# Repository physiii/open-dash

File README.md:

### Objective

Provide an open source platform for vehicle information and entertainment. 

Daughterboard firmware is designed around FreeRTOS. Supports CANbus and J1850 protocols and many functions such as HVAC control, battery monitoring, vehicle status and statistics over wifi. Uses driver circuits for various actuators around the car. 

Front end software is designed to run on Linux. I recommend Ubuntu for the main computer. 

GUI is made using NodeWebkit and communicates with a custom daughterboard for interfacing with the vehicle.

### Install OS
Download ubuntu 21.10 and create boot disk  
Press esc to get to boot menu  
Boot manager  
Choose flash drive  
Choose Install ubuntu
Choose erase disk and install ubuntu  
Remove flash drive and reboot  

### Setup OS
Set no keyring passwd  
Disable Power Savings   
sudo visudo /etc/sudoers: 
```
%sudo   ALL=(ALL:ALL) NOPASSWD:ALL  
```

```
sudo usermod -a -G dialout $USER
sudo usermod -a -G audio $USER
```
Add startup programs  
```
pm2 start /usr/local/src/open-dash/service/index.js --time --name dash
nw /usr/local/src/open-dash
```

### Display

Set scale to 200%  
Rotate to portrait mode
Settings > Appearance > Position on screen: Bottom
```
sudo cp /usr/local/src/open-dash/scripts/99-touch.rules /etc/udev/rules.d/99-touch.rules
```

### Install Dependencies
```
sudo apt install -y curl
curl -sL https://deb.nodesource.com/setup_14.x | sudo -E bash -
sudo apt update
```

```
sudo wget -qnc https://repo.nordvpn.com/deb/nordvpn/debian/pool/main/nordvpn-release_1.0.0_all.deb
sudo dpkg -i ./nordvpn-release_1.0.0_all.deb
```
```
wget -q -O - https://dl-ssl.google.com/linux/linux_signing_key.pub | sudo apt-key add -
echo 'deb [arch=amd64] http://dl.google.com/linux/chrome/deb/ stable main' | sudo tee /etc/apt/sources.list.d/google-chrome.list
sudo apt update
```

```
sudo apt-get -y install gnupg
wget -qO - https://www.mongodb.org/static/pgp/server-4.4.asc | sudo apt-key add -
echo "deb [ arch=amd64,arm64 ] https://repo.mongodb.org/apt/ubuntu focal/mongodb-org/4.4 multiverse" | sudo tee /etc/apt/sources.list.d/mongodb-org-4.4.list
```

```
sudo apt update && sudo apt upgrade -y

sudo apt install -y \
  tmux git nodejs sshfs nmap cmake pv vlc pithos gimp librecad resolvconf openssh-server \
  net-tools v4l-utils clementine net-tools kodi nordvpn vlc-plugin-bittorrent \
  libgconf-2-4 sshpass git nodejs dnsmasq hostapd tmux xdotool libudev-dev \
  python-setuptools python3-dev libssl-dev libasound2-dev nmap ffmpeg \
  build-essential cmake pkg-config libjpeg-dev libtiff5-dev libatomic1 \
  libavcodec-dev libavformat-dev libswscale-dev libv4l-dev libxvidcore-dev libx264-dev libfreetype6-dev \
  libatlas-base-dev gfortran python3-dev libavcodec-dev libavformat-dev python3-pip \
  libasound-dev portaudio19-dev libportaudio2 libportaudiocpp0 \
  google-chrome-stable speedtest-cli mongodb-org \

```

```
sudo npm install -g nw-gyp
sudo npm install -g pm2 --unsafe-perm=true --allow-root
sudo snap install atom --classic
sudo snap install blender --channel=beta --classic
```

```
sudo apt install -y apt-transport-https curl
sudo curl -fsSLo /usr/share/keyrings/brave-browser-archive-keyring.gpg https://brave-browser-apt-release.s3.brave.com/brave-browser-archive-keyring.gpg
echo "deb [signed-by=/usr/share/keyrings/brave-browser-archive-keyring.gpg arch=amd64] https://brave-browser-apt-release.s3.brave.com/ stable main"|sudo tee /etc/apt/sources.list.d/brave-browser-release.list
sudo apt update
sudo apt install -y brave-browser
```
### kicad
```
sudo add-apt-repository --yes ppa:js-reynaud/kicad-5.1
sudo apt update
sudo apt install -y --install-suggests kicad

mkdir ~/circuits
cd ~/circuits
git clone https://github.com/physiii/kicad-parts
# add symbol and footprint paths
```
### esp32
```
sudo ln -s /usr/bin/python3 /usr/bin/python

mkdir -p ~/esp
cd ~/esp
git clone --recursive https://github.com/espressif/esp-idf.git

cd ~/esp/esp-idf
./install.sh

echo "alias get_idf='. $HOME/esp/esp-idf/export.sh'" >> ~/.bashrc

source ~/.bashrc
get_idf

cd ~/esp
cp -r $IDF_PATH/examples/get-started/hello_world .
cd ~/esp/hello_world
idf.py set-target esp32
idf.py menuconfig
```

### audio
```
cd ~
git clone https://github.com/physiii/ardour-sessions

```
sudo nano /etc/security/limits.conf
```
  @audio          -       rtprio          99
```
```
sudo apt install -y qjackctl pulseaudio-module-jack libjack0 jackd jack-tools \
linux-lowlatency ardour a2jmidid libjack-dev pavucontrol \
```
## Jack
set interface  
Settings -> MIDI Driver: seq  
Options -> execute script after startup: pactl load-module module-jack-sink;pactl load-module module-jack-source;pactl set-default-sink jack_out  
Misc -> start JACK audio service on application startup  
```
pamcd set-default-sink jack_out
```
```
sudo apt install -y \
calf-plugins libtool autoconf libexpat1-dev libglib2.0-dev libfluidsynth-dev \
jackd libjack-dev libglade2-dev lv2-dev yoshimi ams \
blop caps cmt fil-plugins rev-plugins swh-plugins tap-plugins \
invada-studio-plugins-lv2 mda-lv2 swh-lv2 \
blepvco mcp-plugins omins so-synth-lv2 lingot \
```
## MIDI

```
pip3 install python-rtmidi pyserial mido
git clone https://github.com/physiii/wireless-midi
```

###  Popcorn
```
sudo chown -R ${USER}:${USER} /usr/local/src
cd /usr/local/src
git clone https://github.com/popcorn-official/popcorn-desktop
cd popcorn-desktop
sudo npm install -g gulp
npm install
gulp build
gulp run
nw .
```
### NW.JS
```
sudo chown -R ${USER}:${USER} /usr/local/src
cd /usr/local/src  
wget https://dl.nwjs.io/v0.54.0/nwjs-sdk-v0.54.0-linux-x64.tar.gz
tar -zxvf nwjs-sdk*  
cd nwjs-sdk*  
sudo ln -s /usr/local/src/nwjs-sdk-v0.54.0-linux-x64/nw /usr/bin/nw  
```
### Install Software
```
sudo chown -R ${USER}:${USER} /usr/local/src
cd /usr/local/src
git clone https://github.com/physiii/open-dash
cd open-dash
npm install
npm run build
```

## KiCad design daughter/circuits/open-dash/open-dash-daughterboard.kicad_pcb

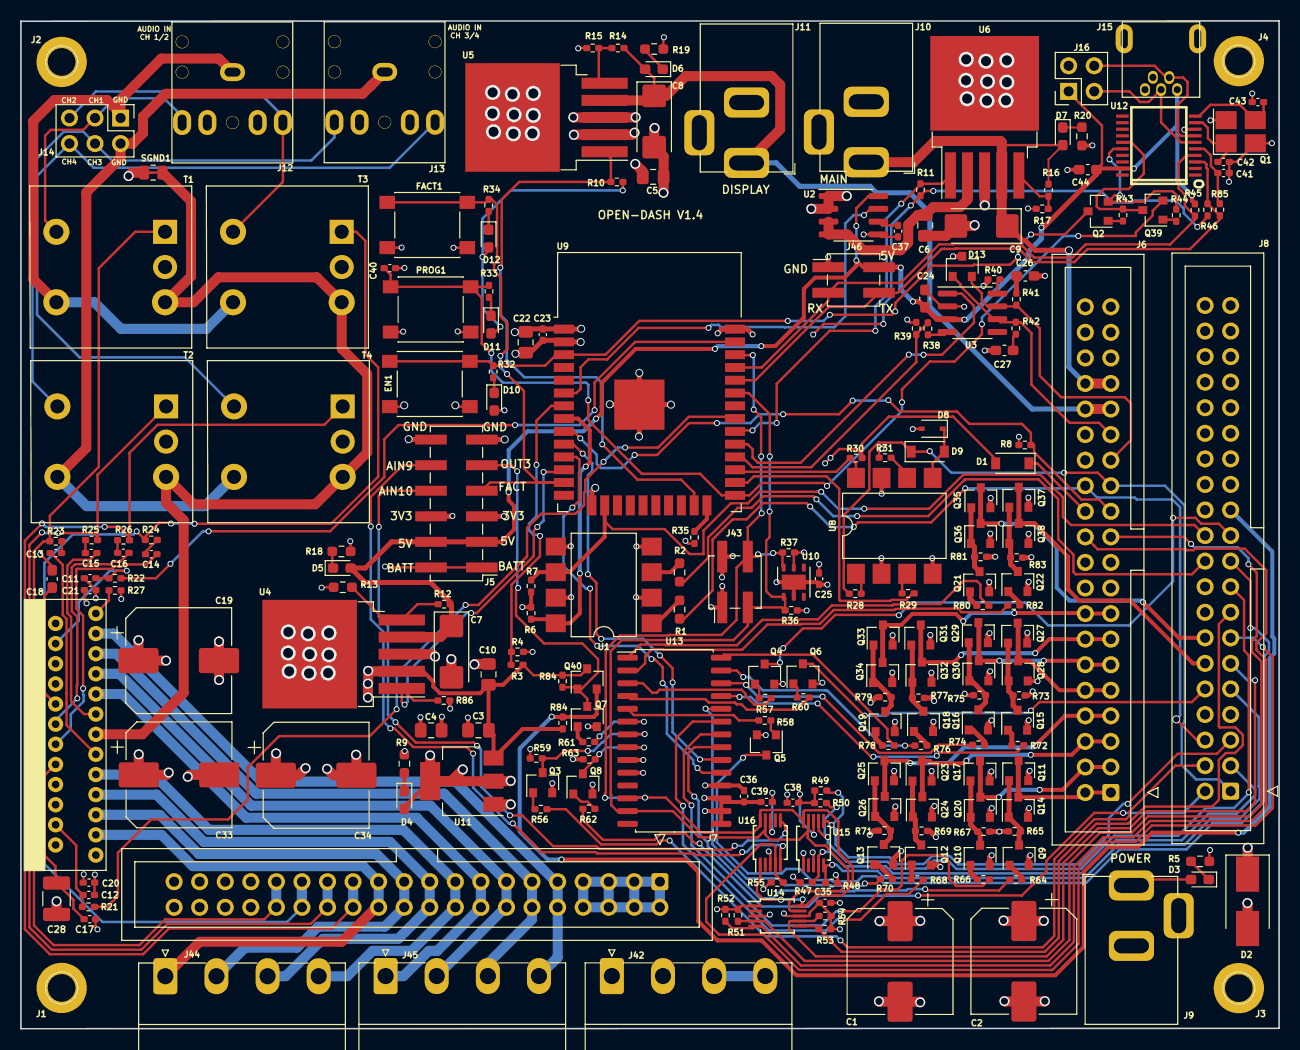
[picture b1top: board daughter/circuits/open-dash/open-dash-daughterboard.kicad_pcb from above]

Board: 4 copper layers, 125.0 x 100.1 mm, 225 parts (0 on the bottom side), 170 nets.

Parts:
C1, C2, C19, C33, C34: C_470uF; CP_Elec_10x10
C3, C4, C5, C6, C10, C22: C_10uF; C_0805_2012Metric_Pad1.18x1.45mm_HandSolder
C7, C8, C9: C_10uF_Ta; CP_EIA-6032-15_Kemet-U_Pad2.25x2.35mm_HandSolder
C11, C12, C17, C20, C23, C40: C_1uF; C_0402_1005Metric_Pad0.74x0.62mm_HandSolder
C13, C14, C15, C16, C21, C25: C_0.1uF; C_0402_1005Metric_Pad0.74x0.62mm_HandSolder
C18: C_470nF; C_0603_1608Metric_Pad1.08x0.95mm_HandSolder
C24: C_0.1uF; C_0603_1608Metric_Pad1.08x0.95mm_HandSolder
C26, C27: C_470pF; C_0603_1608Metric_Pad1.08x0.95mm_HandSolder
C28: C_47uF; C_1210_3225Metric_Pad1.33x2.70mm_HandSolder
C35, C36, C38, C39, C41: C_100nF_0402; C_0402_1005Metric_Pad0.74x0.62mm_HandSolder
C37: C_1nF_0402; C_0402_1005Metric_Pad0.74x0.62mm_HandSolder
C42, C43: C_27pF_0402; C_0402_1005Metric_Pad0.74x0.62mm_HandSolder
C44: C_22uF; C_0603_1608Metric_Pad1.08x0.95mm_HandSolder
D1, D9: D_B5819W; D_SOD-123
D2: D_Zener; D_SMB_Handsoldering
D3, D4, D5, D6, D7: LED_G; LED_0603_1608Metric_Pad1.05x0.95mm_HandSolder
D8: MM3Z8V2; D_SOD-323
D10, D11, D12: LED_G; D_0603_1608Metric_Pad1.05x0.95mm_HandSolder
D13: PESD1CAN-UX; SOT-23
EN1: SW_PUSH; SW_SPST_PTS645
FACT1: SW_PUSH; SW_SPST_PTS645
J1, J2, J3, J4: Conn_01x01_Female; Mount_Hole
J5: Conn_02x06_Odd_Even; PinHeader_2x06_P2.54mm_Vertical_SMD
J6, J7, J8: Conn_IDE_40; IDC-Header_2x20_P2.54mm_Vertical
J9, J10, J11: Barrel_Jack_OD5.5_ID2.5; BarrelJack_OD5.5_ID2.5
J12, J13: AudioJack_3.5TRS; AudioJack_SJ1-3525N
J14: Conn_02x03_Odd_Even; PinHeader_2x03_P2.54mm_Vertical
J15: USB_MINI_B; USB-mini-B-0548190519
J16: Conn_02x02_Counter_Clockwise; PinHeader_2x02_P2.54mm_Vertical
J42, J44, J45: Terminal_01x04; Terminal_1,5_4-G-5.08_1x04_P5.08mm_Horizontal
J43, J46: Conn_02x02_Counter_Clockwise; PinHeader_2x02_P2.54mm_Vertical_SMD
PROG1: SW_PUSH; SW_SPST_PTS645
Q1: Crystal_12Mhz; Crystal_SMD_3225-4Pin_3.2x2.5mm_HandSoldering
Q2: Q_SS8050; SOT-23
Q3, Q4, Q5, Q6, Q7, Q8, Q9, Q10, Q12, Q13, Q15, Q16, Q18, Q19, Q21, Q22: Q_NPN_BEC; SOT-23
Q11, Q17, Q23, Q25, Q27, Q29, Q31, Q33, Q35, Q37, Q40: Q_AO3401A; SOT-23
Q14, Q20, Q24, Q26, Q28, Q30, Q32, Q34, Q36, Q38: Q_AO3400A; SOT-23
Q39: Q_SS8550; SOT-23
R1, R2, R5, R9, R18, R19, R20: R_1K; R_0603_1608Metric_Pad0.98x0.95mm_HandSolder
R3: R_100K_0402; R_0402_1005Metric_Pad0.72x0.64mm_HandSolder
R4, R6, R7, R10, R11, R21, R32, R33, R34, R35, R36, R37, R39, R45, R46, R47, R48, R49, R50, R51, R52, R53, R54, R55, R56, R57, R58, R59, R60, R61, R62, R63, R64, R65, R66, R67, R68, R69, R70, R71, R72, R73, R74, R75, R76, R77, R78, R79, R80, R81, R82, R83, R84#2, R85, R86: R_10K_0402; R_0402_1005Metric_Pad0.72x0.64mm_HandSolder
R8, R23, R24, R25, R26, R28, R30, R31, R43, R44, R84: R_1K_0402; R_0402_1005Metric_Pad0.72x0.64mm_HandSolder
R12, R14, R16: R_20K; R_0402_1005Metric_Pad0.72x0.64mm_HandSolder
R13: R_6.8K; R_0603_1608Metric_Pad0.98x0.95mm_HandSolder
R15, R17: R_2.2K; R_0402_1005Metric_Pad0.72x0.64mm_HandSolder
R22, R27: R_47K_0402; R_0402_1005Metric_Pad0.72x0.64mm_HandSolder
R29, R41, R42: R_100; R_0402_1005Metric_Pad0.72x0.64mm_HandSolder
R38, R40: R_4.7K; R_0402_1005Metric_Pad0.72x0.64mm_HandSolder
SGND1: SGND_CONN
T1, T2, T3, T4: Audio_Transformer
U1, U8: Opto_TLP521; SMDIP-8_W9.53mm
U2: ACS711; SOIC-8_3.9x4.9mm_P1.27mm
U3: CAN_MCP2551-I-SN; SOIC-8_3.9x4.9mm_P1.27mm
U4, U5, U6: MIC29302WU; TO-263-5_TabPin3
U7: TDA7851F; Flexiwatt25-V
U9: ESP32-WROOM-32
U10: Temp_Hum_HDC1080DMBR; DFN-6-1EP_3x3mm_P1mm_EP1.5x2.4mm
U11: REG_AMS1117-3.3; SOT-223-3_TabPin2
U12: CH340T(SSOP20W); SSOP-20W
U13: MCP23017_SS; SOIC-28W_7.5x17.9mm_P1.27mm
U14, U15, U16: ADC_ADS1015; MSOP-10_3x3mm_P0.5mm

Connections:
/3V3: C4.1, C22.1, C23.1, C25.1, C35.1, C36.1, C38.1, C39.1, D1.2, D4.2, D10.2, D11.2, D12.2, J5.5, J5.6, J43.2, R6.2, R7.2, R10.2, R11.2, R30.1, R36.1, R37.2, R46.2, R47.2, R48.2, R49.2, R50.2, R51.2, R52.2, R53.2, R54.2, R55.2, R59.2, R63.2, R86.2, U9.2, U10.5, U11.2, U13.9, U13.18, U14.1, U14.8, U15.8, U16.8
/5V: C7.1, C24.1, C44.1, D5.2, J5.3, J5.4, J15.1, J16.1, J46.2, R12.1, R45.1, U2.8, U3.3, U4.4, U12.19
/5V_EN: R86.1, U4.1, U9.12
/AIN9: J5.10, U16.5
/AIN10: J5.8, U16.6
/AMBIENT_AIR_TEMP: J8.9, R48.1, U15.5
/AMBIENT_LIGHT: J8.15, R53.1, U14.6
/AUDIO_IN1: J7.31, J7.32, R23.2, T1.5
/AUDIO_IN2: J7.29, J7.30, R24.2, T3.5
/AUDIO_IN3: J7.27, J7.28, R25.2, T2.5
/AUDIO_IN4: J7.25, J7.26, R26.2, T4.5
/AUDIO_MUTE: R22.2, U9.37
/AUDIO_STBY: R21.1, U9.31
/Audio Amplifier/AC_GND: C18.1, U7.16
/Audio Amplifier/AUDIO_GND1: J12.1, J14.1, T1.2, T3.2
/Audio Amplifier/AUDIO_GND2: J13.1, J14.2, T2.2, T4.2
/Audio Amplifier/IN1: J12.3, J14.3, T1.1
/Audio Amplifier/IN2: J12.2, J14.5, T3.1
/Audio Amplifier/IN3: J13.3, J14.4, T2.1
/Audio Amplifier/IN4: J13.2, J14.6, T4.1
/Audio Amplifier/MUTE: C11.2, R22.1, U7.22
/Audio Amplifier/OD: R27.2, U7.25
/Audio Amplifier/STBY: C12.2, R21.2, U7.4
/Audio Amplifier/SVR: C17.1, C28.1, U7.10
/BATTERY: C1.1, C2.1, C3.1, C5.1, C10.1, C19.1, C20.2, C21.1, C33.1, C34.1, D2.1, D3.2, J5.1, J5.2, J6.17, J6.18, J6.19, J6.20, J6.28, J7.1, J7.2, J7.3, J7.4, J7.5, J7.6, J7.7, J7.8, J8.8, J8.18, J8.27, J8.28, J8.29, J8.30, J8.31, J8.32, J9.1, J42.3, J42.4, Q11.2, Q17.2, Q23.2, Q25.2, Q27.2, Q29.2, Q31.2, Q33.2, Q35.2, Q37.2, Q40.3, R3.1, R31.1, R65.2, R67.2, R69.2, R71.2, R73.2, R75.2, R77.2, R79.2, R81.2, R83.2, R84.1, R84#2.2, U2.1, U2.2, U4.2, U5.2, U7.6, U7.20, U11.3
/BATTERY_VOLTAGE_SENSE: R3.2, R4.1, U9.7
/BLOWER_MOTOR: J8.10, Q6.3
/CAN+: D13.2, J6.27, R41.2, U3.7
/CAN-: D13.1, J6.29, R42.2, U3.6
/CAN_RX: R38.1, R39.2, U9.28
/CAN_TX: U3.1, U9.29
/CANbus/RX: R38.2, U3.4
/CURRENT_SENSE: U2.7, U9.6
/C_OUT3: J5.9, Q7.3, Q40.1, R84#2.1
/DISPLAY_EN: R10.1, U5.1, U9.23
/DISPLAY_POWER: C8.1, D6.2, J6.31, J6.32, J11.1, R14.1, U5.4
/DRIVER_HEATED_SEAT_STATUS: J8.4, R56.1
/DRIVER_SEAT_TEMP_CONTROL: J8.14, Q35.3, Q36.3
/DRIVER_SUNLOAD: J8.11, R54.1, U14.7
/ESP_EN: EN1.1, Q2.3, R32.1, U9.3
/EXT_AMP_ON: J8.23, Q40.2, R84.2
/FACT: FACT1.1, J5.7, R34.1, U9.13
/HVAC/A0: R64.1, U13.21
/HVAC/A1: R66.1, U13.22
/HVAC/A2: R68.1, U13.23
/HVAC/A3: R70.1, U13.24
/HVAC/A4: R72.1, U13.25
/HVAC/A5: R74.1, U13.26
/HVAC/A6: R76.1, U13.27
/HVAC/A7: R78.1, U13.28
/HVAC/B0: R80.1, U13.1
/HVAC/B1: R82.1, U13.2
/HVAC/B2: R57.1, U13.3
/HVAC/B3: R60.1, U13.4
/HVAC/B4: R58.1, U13.5
/HVAC/B5: R61.1, U13.6
/HVAC/B6: Q3.3, R59.1, U13.7
/HVAC/B7: Q8.3, R63.1, U13.8
/HVAC/H-Bridge/C1: Q9.3, Q11.1, Q14.1, R65.1
/HVAC/H-Bridge/C2: Q10.3, Q17.1, Q20.1, R67.1
/HVAC/sheet607B7BA9/C1: Q21.3, Q35.1, Q36.1, R81.1
/HVAC/sheet607B7BA9/C2: Q22.3, Q37.1, Q38.1, R83.1
/HVAC/sheet60537A7E/C1: Q15.3, Q27.1, Q28.1, R73.1
/HVAC/sheet60537A7E/C2: Q16.3, Q29.1, Q30.1, R75.1
/HVAC/sheet60537FF7/C1: Q18.3, Q31.1, Q32.1, R77.1
/HVAC/sheet60537FF7/C2: Q19.3, Q33.1, Q34.1, R79.1
/HVAC/sheet6051923C/C1: Q12.3, Q23.1, Q24.1, R69.1
/HVAC/sheet6051923C/C2: Q13.3, Q25.1, Q26.1, R71.1
/IGNITION: J6.26, J8.6, R1.2
/IGNITION_SENSE: R6.1, U1.8, U9.8
/INSIDE_AIR_TEMP: J8.3, R47.1, U15.4
/INSIDE_AIR_TEMP_BLOWER: J8.21, Q4.3
/INTA: U9.10, U13.20
/INTB: U9.11, U13.19
/J1850: D9.1, J6.25, J8.1, R28.2
/J1850_RX: R30.2, U8.8, U9.27
/J1850_TX: R29.1, U9.26
/LEFT_AIR_TEMP_CONTROL_A: J6.1, J6.2, Q11.3, Q14.3
/LEFT_AIR_TEMP_CONTROL_B: J6.3, J6.4, Q17.3, Q20.3
/LF+: J7.17, J7.18, J44.4, U7.9
/LF-: J7.19, J7.20, J44.3, U7.7
/LOWER_LEFT_AIR_TEMP: J6.22, R52.1, U14.5
/LOWER_RIGHT_AIR_TEMP: J6.21, R51.1, U14.4
/LR+: J7.15, J7.16, J45.1, U7.17
/LR-: J7.13, J7.14, J45.2, U7.19
/MAIN_EN: R11.1, U6.1, U9.30
/MAIN_POWER: C9.1, D7.2, J6.33, J6.34, J10.1, R16.1, U6.4
/MODE_A: J6.9, J6.10, Q27.3, Q28.3
/MODE_B: J6.11, J6.12, Q29.3, Q30.3
/Microcontroller/IO2: R35.1, U9.24
/PASSENGER_HEATED_SEAT_STATUS: J8.2, R62.1
/PASSENGER_SEAT_TEMP_CONTROL: J8.12, Q37.3, Q38.3
/PASSENGER_SUNLOAD: J8.13, R55.1, U16.4
/PROG: C40.1, PROG1.1, Q39.2, R33.1, U9.25
/Power/MAIN_POWER_IN: C6.1, U2.3, U2.4, U6.2
/REAR_DEFOG: J8.19, Q5.3
/RECIRCULATION_A: J6.13, J6.14, Q31.3, Q32.3
/RECIRCULATION_B: J6.15, J6.16, Q33.3, Q34.3
/RF+: J7.21, J7.22, J44.2, U7.5
/RF-: J7.23, J7.24, J44.1, U7.3
/RIGHT_AIR_TEMP_CONTROL_A: J6.5, J6.6, Q23.3, Q24.3
/RIGHT_AIR_TEMP_CONTROL_B: J6.7, J6.8, Q25.3, Q26.3
/RR+: J7.11, J7.12, J45.3, U7.21
/RR-: J7.9, J7.10, J45.4, U7.23
/RXD: J46.4, R46.1, R85.2, U9.34, U12.3
/SCL: J43.4, R37.1, U9.36, U10.6, U13.12, U14.10, U15.10, U16.1, U16.10
/SDA: J43.3, R36.2, U9.33, U10.1, U13.13, U14.9, U15.9, U16.9
/SENSE1: J8.22, R7.1, U1.6, U9.16
/TRIGGER1: J8.20, R2.2
/TXD: J46.3, R45.2, U9.35, U12.4
/UPPER_LEFT_AIR_TEMP: J8.17, R50.1, U15.7
/UPPER_RIGHT_AIR_TEMP: J8.5, R49.1, U15.6
/USB/D+: J15.3, J16.3, U12.6
/USB/D-: J15.2, J16.4, U12.7
/WHEEL_CONTROLS_SIGNAL: J6.23, R8.2, U9.9
/WHEEL_CONTROLS_SUPPLY: D1.1, J6.24
GND: C1.2, C2.2, C3.2, C4.2, C5.2, C6.2, C7.2, C8.2, C9.2, C10.2, C11.1, C12.1, C17.2, C18.2, C19.2, C20.1, C21.2, C22.2, C23.2, C24.2, C25.2, C26.2, C27.2, C28.2, C33.2, C34.2, C35.2, C36.2, C37.2, C38.2, C39.2, C40.2, C41.2, C42.2, C43.2, C44.2, D2.2, D8.2, D13.3, EN1.2, FACT1.2, J1.1, J2.1, J3.1, J4.1, J5.11, J5.12, J6.30, J6.35, J6.36, J6.37, J6.38, J6.39, J6.40, J7.33, J7.34, J7.35, J7.36, J7.37, J7.38, J7.39, J7.40, J8.7, J8.24, J8.25, J8.26, J8.33, J8.34, J8.35, J8.36, J8.37, J8.38, J8.39, J8.40, J9.2, J9.3, J10.2, J10.3, J11.2, J11.3, J15.5, J16.2, J42.1, J42.2, J43.1, J46.1, PROG1.2, Q1.2, Q1.4, Q3.2, Q4.2, Q5.2, Q6.2, Q7.2, Q8.2, Q9.2, Q10.2, Q12.2, Q13.2, Q14.2, Q15.2, Q16.2, Q18.2, Q19.2, Q20.2, Q21.2, Q22.2, Q24.2, Q26.2, Q28.2, Q30.2, Q32.2, Q34.2, Q36.2, Q38.2, R4.2, R5.1, R8.1, R9.2, R13.2, R15.2, R17.2, R18.2, R19.2, R20.2, R27.1, R35.2, R39.1, R40.1, SGND1.1, U1.2, U1.4, U1.5, U1.7, U2.5, U3.2, U4.3, U5.3, U6.3, U7.1, U7.2, U7.8, U7.18, U7.24, U8.2, U8.4, U8.7, U9.1, U9.15, U9.38, U9.39, U10.2, U10.7, U11.1, U12.8, U13.10, U13.15, U13.16, U13.17, U14.3, U15.1, U15.3, U16.3
GNDS: SGND1.2, T1.3, T2.3, T3.3, T4.3, U7.13
unnamed: C13.1, U7.11
unnamed: C13.2, R23.1
unnamed: C14.1, U7.12
unnamed: C14.2, R24.1
unnamed: C15.1, U7.15
unnamed: C15.2, R25.1
unnamed: C16.1, U7.14
unnamed: C16.2, R26.1
unnamed: C26.1, R41.1
unnamed: C27.1, R42.1
unnamed: C37.1, U2.6
unnamed: C41.1, R85.1, U12.5
unnamed: C42.1, Q1.1, U12.9
unnamed: C43.1, Q1.3, U12.10
unnamed: D3.1, R5.2
unnamed: D4.1, R9.1
unnamed: D5.1, R18.1
unnamed: D6.1, R19.1
unnamed: D7.1, R20.1
unnamed: D8.1, D9.2, U8.5
unnamed: D10.1, R32.2
unnamed: D11.1, R33.2
unnamed: D12.1, R34.2
unnamed: Q2.1, R43.1
unnamed: Q2.2, R44.2, U12.16
unnamed: Q3.1, R56.2
unnamed: Q4.1, R57.2
unnamed: Q5.1, R58.2
unnamed: Q6.1, R60.2
unnamed: Q7.1, R61.2
unnamed: Q8.1, R62.2
unnamed: Q9.1, R64.2
unnamed: Q10.1, R66.2
unnamed: Q12.1, R68.2
unnamed: Q13.1, R70.2
unnamed: Q15.1, R72.2
unnamed: Q16.1, R74.2
unnamed: Q18.1, R76.2
unnamed: Q19.1, R78.2
unnamed: Q21.1, R80.2
unnamed: Q22.1, R82.2
unnamed: Q39.1, R44.1
unnamed: Q39.3, R43.2, U12.15
unnamed: R1.1, U1.1
unnamed: R2.1, U1.3
unnamed: R12.2, R13.1, U4.5
unnamed: R14.2, R15.1, U5.5
unnamed: R16.2, R17.1, U6.5
unnamed: R28.1, U8.1
unnamed: R29.2, U8.3
unnamed: R31.2, U8.6
unnamed: R40.2, U3.8

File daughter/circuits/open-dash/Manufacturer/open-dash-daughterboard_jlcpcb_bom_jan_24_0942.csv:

Comment,Designator,Footprint,LCSC
"C_0.1uF","C13,C14,C15,C16,C21,C25","Capacitor_SMD:C_0402_1005Metric_Pad0.74x0.62mm_HandSolder","C1525"
"C_470nF","C18","Capacitor_SMD:C_0603_1608Metric_Pad1.08x0.95mm_HandSolder","C1623"
"C_470uF","C1,C2,C19,C33,C34","Capacitor_SMD:CP_Elec_10x10","C3350"
"C_1uF","C11,C12,C20,C23,C40","Capacitor_SMD:C_0402_1005Metric_Pad0.74x0.62mm_HandSolder","C52923"
"C_0.1uF","C24","Capacitor_SMD:C_0603_1608Metric_Pad1.08x0.95mm_HandSolder","C14663"
"C_470pF","C26,C27","Capacitor_SMD:C_0603_1608Metric_Pad1.08x0.95mm_HandSolder","C1537"
"C_1nF_0402","C37","Capacitor_SMD:C_0402_1005Metric_Pad0.74x0.62mm_HandSolder","C1523"
"C_10uF","C3,C4,C5,C6,C10,C17,C22","Capacitor_SMD:C_0805_2012Metric_Pad1.18x1.45mm_HandSolder","C15850"
"C_100nF_0402","C35,C36,C38,C39,C41","Capacitor_SMD:C_0402_1005Metric_Pad0.74x0.62mm_HandSolder","C1525"
"C_27pF_0402","C42,C43","Capacitor_SMD:C_0402_1005Metric_Pad0.74x0.62mm_HandSolder","C1557"
"C_22uF","C44","Capacitor_SMD:C_0603_1608Metric_Pad1.08x0.95mm_HandSolder","C59461"
"C_10uF_Ta","C7,C8,C9","Capacitor_Tantalum_SMD:CP_EIA-6032-15_Kemet-U_Pad2.25x2.35mm_HandSolder","C116748"
"D_B5819W","D1,D9","Diode_SMD:D_SOD-123","C8598"
"LED_G","D10,D11,D12","Diode_SMD:D_0603_1608Metric_Pad1.05x0.95mm_HandSolder","C72041"
"PESD1CAN-UX","D13","Package_TO_SOT_SMD:SOT-23","C152727"
"D_Zener","D2","Diode_SMD:D_SMB_Handsoldering","C8835"
"LED_G","D3,D4,D5,D6,D7","LED_SMD:LED_0603_1608Metric_Pad1.05x0.95mm_HandSolder","C72041"
"MM3Z8V2","D8","Diode_SMD:D_SOD-323","C216751"
"SW_PUSH","FACT1,PROG1,EN1","Button_Switch_SMD:SW_SPST_PTS645","C127509"
"Conn_01x01_Female","J1,J2,J3,J4,J38,J39,J40,J41","Open_Automation:Mount_Hole",""
"Barrel_Jack_OD5.5_ID2.5","J9,J10,J11","Open_Automation:BarrelJack_OD5.5_ID2.5",""
"AudioJack_3.5TRS","J12,J13","Open_Automation:AudioJack_SJ1-3525N",""
"Conn_02x03_Odd_Even","J14","Connector_PinHeader_2.54mm:PinHeader_2x03_P2.54mm_Vertical",""
"USB_MINI_B","J15","Open_Automation:USB-mini-B-0548190519",""
"Conn_02x02_Counter_Clockwise","J16","Connector_PinHeader_2.54mm:PinHeader_2x02_P2.54mm_Vertical",""
"Conn_01x08","J17,J19,J23,J25,J29,J31","Connector_PinHeader_2.54mm:PinHeader_1x08_P2.54mm_Vertical",""
"C1","J18","Open_Automation:Conn_HVAC",""
"C2","J24","Open_Automation:Conn_HVAC",""
"Conn_01x20","J20,J21,J26,J28,J33,J34","Connector_PinHeader_2.54mm:PinHeader_1x20_P2.54mm_Vertical",""
"C3","J30","Open_Automation:Conn_HVAC",""
"Conn_01x12","J35,J37","Connector_PinHeader_2.54mm:PinHeader_1x12_P2.54mm_Vertical",""
"STEREO","J36","Open_Automation:Conn_Stereo",""
"Conn_02x02_Counter_Clockwise","J43,J46","Connector_PinHeader_2.54mm:PinHeader_2x02_P2.54mm_Vertical_SMD",""
"Terminal_01x04","J42,J44,J45","Open_Automation:Terminal_1,5_4-G-5.08_1x04_P5.08mm_Horizontal",""
"Conn_02x06_Odd_Even","J5","Connector_PinHeader_2.54mm:PinHeader_2x06_P2.54mm_Vertical_SMD",""
"Conn_IDE_40","J6,J7,J8,J22,J27,J32","Connector_IDC:IDC-Header_2x20_P2.54mm_Vertical",""
"Crystal_12Mhz","Q1","Crystal:Crystal_SMD_3225-4Pin_3.2x2.5mm_HandSoldering","C9002"
"Q_AO3400A","Q14,Q20,Q24,Q26,Q28,Q30,Q32,Q34,Q36,Q38","Package_TO_SOT_SMD:SOT-23","C20917"
"Q_SS8050","Q2","Package_TO_SOT_SMD:SOT-23","C2150"
"Q_SS8550","Q39","Package_TO_SOT_SMD:SOT-23","C8542"
"Q_NPN_BEC","Q3,Q4,Q5,Q6,Q7,Q8,Q9,Q10,Q12,Q13,Q15,Q16,Q18,Q19,Q21,Q22","Package_TO_SOT_SMD:SOT-23","C2150"
"Q_AO3401A","Q11,Q17,Q23,Q25,Q27,Q29,Q31,Q33,Q35,Q37,Q40","Package_TO_SOT_SMD:SOT-23","C15127"
"R_6.8K","R13","Resistor_SMD:R_0603_1608Metric_Pad0.98x0.95mm_HandSolder","C23212"
"R_20K","R12,R14,R16","Resistor_SMD:R_0402_1005Metric_Pad0.72x0.64mm_HandSolder","C25765"
"R_2.2K","R15,R17","Resistor_SMD:R_0402_1005Metric_Pad0.72x0.64mm_HandSolder","C4190"
"R_1K","R1,R2,R5,R9,R18,R19,R20","Resistor_SMD:R_0603_1608Metric_Pad0.98x0.95mm_HandSolder"," C21190"
"R_47K_0402","R22,R27","Resistor_SMD:R_0402_1005Metric_Pad0.72x0.64mm_HandSolder","C25792"
"R_100","R29,R41,R42","Resistor_SMD:R_0402_1005Metric_Pad0.72x0.64mm_HandSolder","C25076"
"R_100K_0402","R3","Resistor_SMD:R_0402_1005Metric_Pad0.72x0.64mm_HandSolder","C25741"
"R_4.7K","R38,R40","Resistor_SMD:R_0402_1005Metric_Pad0.72x0.64mm_HandSolder","C25900"
"R_1K_0402","R8,R23,R24,R25,R26,R28,R30,R31,R43,R44","Resistor_SMD:R_0402_1005Metric_Pad0.72x0.64mm_HandSolder","C11702"
"R_10K_0402","R4,R6,R7,R10,R11,R21,R32,R33,R34,R35,R36,R37,R39,R45,R46,R47,R48,R49,R50,R51,R52,R53,R54,R55,R56,R57,R58,R59,R60,R61,R62,R63,R64,R65,R66,R67,R68,R69,R70,R71,R72,R73,R74,R75,R76,R77,R78,R79,R80,R81,R82,R83,R84,R85,R86","Resistor_SMD:R_0402_1005Metric_Pad0.72x0.64mm_HandSolder","C25744"
"SGND_CONN","SGND1","Open_Automation:SGND_CONN",""
"Audio_Transformer","T1,T2,T3,T4","Open_Automation:Audio_Transformer",""
"Opto_TLP521","U1,U8","Package_DIP:SMDIP-8_W9.53mm","C722233"
"Temp_Hum_HDC1080DMBR","U10","Package_DFN_QFN:DFN-6-1EP_3x3mm_P1mm_EP1.5x2.4mm","C82227"
"REG_AMS1117-3.3","U11","Package_TO_SOT_SMD:SOT-223-3_TabPin2","C347222"
"CH340T(SSOP20W)","U12","Open_Automation:SSOP-20W","C8689"
"MCP23017_SS","U13","Package_SO:SOIC-28W_7.5x17.9mm_P1.27mm","C47023"
"ADC_ADS1015","U14,U15,U16","Package_SO:MSOP-10_3x3mm_P0.5mm","C37593"
"ACS711","U2","Package_SO:SOIC-8_3.9x4.9mm_P1.27mm","C10681"
"CAN_MCP2551-I-SN","U3","Package_SO:SOIC-8_3.9x4.9mm_P1.27mm","C7376"
"MIC29302WU","U4,U5,U6","Package_TO_SOT_SMD:TO-263-5_TabPin3","C11149"
"TDA7851F","U7","Open_Automation:Flexiwatt25-V",""
"ESP32-WROOM-32","U9","RF_Module:ESP32-WROOM-32","C82899"

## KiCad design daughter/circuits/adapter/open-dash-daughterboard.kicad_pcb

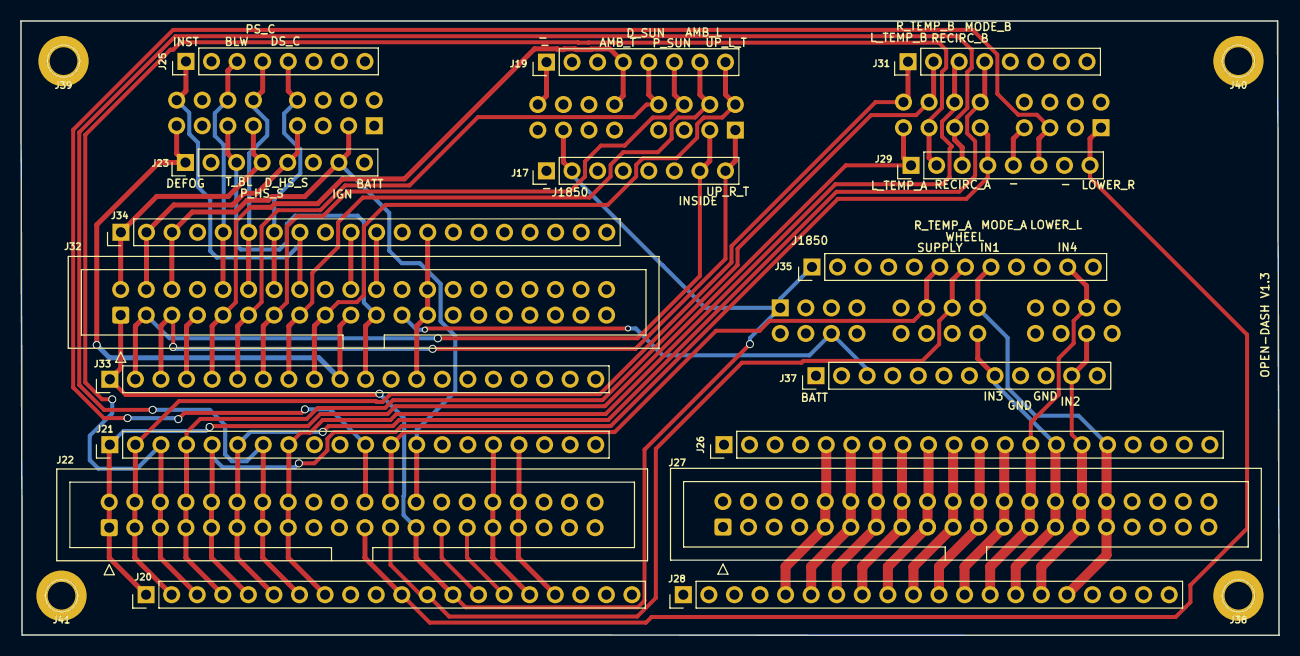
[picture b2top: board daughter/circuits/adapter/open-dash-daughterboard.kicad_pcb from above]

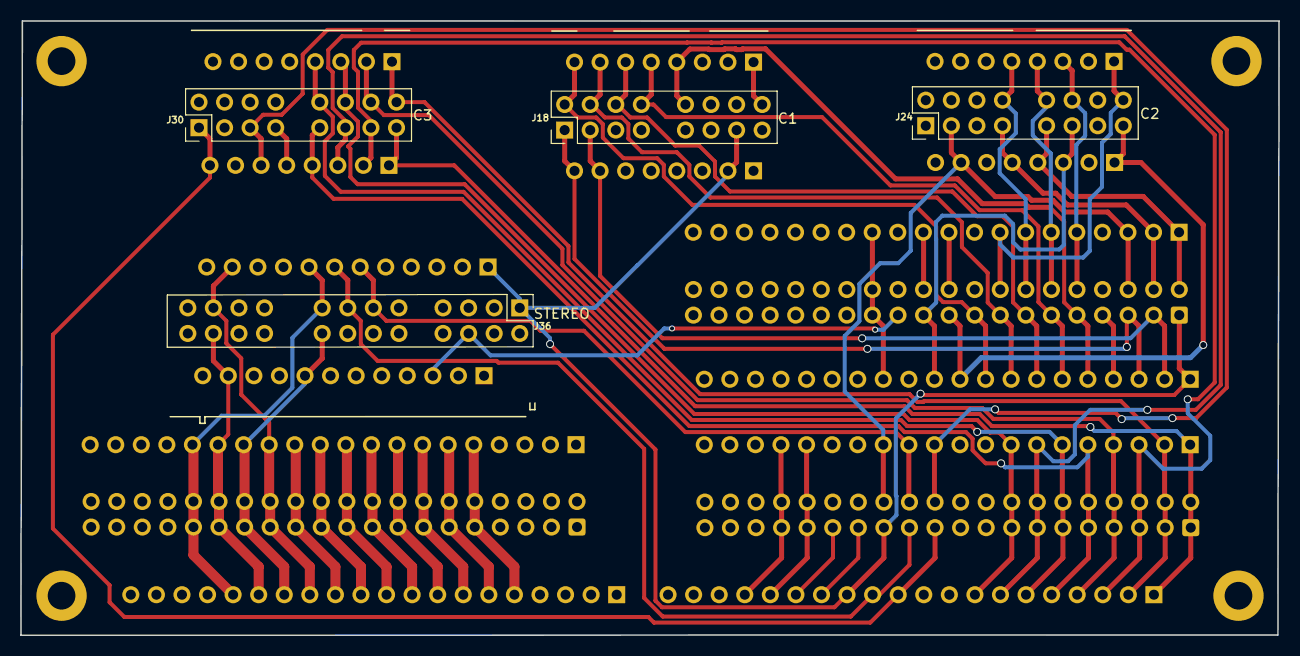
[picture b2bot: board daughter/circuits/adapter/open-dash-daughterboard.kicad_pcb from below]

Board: 4 copper layers, 125.0 x 61.0 mm, 25 parts (4 on the bottom side), 50 nets.

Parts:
J17, J19, J23, J25, J29, J31: Conn_01x08; PinHeader_1x08_P2.54mm_Vertical
J18: C1; Conn_HVAC
J20, J21, J26, J28, J33, J34: Conn_01x20; PinHeader_1x20_P2.54mm_Vertical
J22, J27, J32: Conn_IDE_40; IDC-Header_2x20_P2.54mm_Vertical
J24: C2; Conn_HVAC
J30: C3; Conn_HVAC
J35, J37: Conn_01x12; PinHeader_1x12_P2.54mm_Vertical
J36: STEREO; Conn_Stereo
J38, J39, J40, J41: Conn_01x01_Female; Mount_Hole

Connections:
/Interface/AMBIENT_AIR_TEMP: J18.12, J19.4, J32.9, J33.5
/Interface/AMBIENT_LIGHT: J18.15, J19.7, J32.15, J33.8
/Interface/AUDIO_IN1: J26.16, J27.31, J27.32, J28.16, J35.8, J36.8
/Interface/AUDIO_IN2: J26.15, J27.29, J27.30, J28.15, J36.23, J37.11
/Interface/AUDIO_IN3: J26.14, J27.27, J27.28, J28.14, J36.20, J37.8
/Interface/AUDIO_IN4: J26.13, J27.25, J27.26, J28.13, J35.11, J36.11
/Interface/BATTERY: J20.9, J20.10, J21.9, J21.10, J21.14, J22.17, J22.18, J22.19, J22.20, J22.28, J23.8, J24.8, J26.1, J26.2, J26.3, J26.4, J27.1, J27.2, J27.3, J27.4, J27.5, J27.6, J27.7, J27.8, J28.1, J28.2, J28.3, J28.4, J32.8, J32.18, J32.27, J32.28, J32.29, J32.30, J32.31, J32.32, J33.14, J33.15, J33.16, J34.4, J34.9, J34.14, J34.15, J34.16, J36.13, J37.1
/Interface/BLOWER_MOTOR: J24.11, J25.3, J32.10, J34.5
/Interface/CAN+: J20.14, J22.27
/Interface/CAN-: J20.15, J22.29
/Interface/DISPLAY_POWER: J20.16, J21.16, J22.31, J22.32
/Interface/DRIVER_HEATED_SEAT_STATUS: J23.5, J24.5, J32.4, J34.2
/Interface/DRIVER_SEAT_TEMP_CONTROL: J24.13, J25.5, J32.14, J34.7
/Interface/DRIVER_SUNLOAD: J18.13, J19.5, J32.11, J33.6
/Interface/EXT_AMP_ON: J32.23, J36.15, J37.3
/Interface/IGNITION: J21.13, J22.26, J23.7, J24.7, J32.6, J34.3
/Interface/INSIDE_AIR_TEMP: J17.7, J18.7, J32.3, J33.2
/Interface/INSIDE_AIR_TEMP_BLOWER: J23.3, J24.3, J32.21, J33.11
/Interface/INSTRUMENT_SUPPLY_VOLTAGE_4: J24.9, J25.1, J32.16, J34.8
/Interface/J1850: J17.2, J18.2, J20.13, J22.25, J32.1, J33.1, J35.1, J36.1
/Interface/LEFT_AIR_TEMP_CONTROL_A: J20.1, J21.1, J22.1, J22.2, J29.1, J30.1
/Interface/LEFT_AIR_TEMP_CONTROL_B: J20.2, J21.2, J22.3, J22.4, J30.9, J31.1
/Interface/LF+: J26.9, J27.17, J27.18, J28.9
/Interface/LF-: J26.10, J27.19, J27.20, J28.10
/Interface/LOWER_LEFT_AIR_TEMP: J21.11, J22.22, J29.6, J30.6
/Interface/LOWER_RIGHT_AIR_TEMP: J20.11, J22.21, J29.8, J30.8
/Interface/LR+: J26.8, J27.15, J27.16, J28.8
/Interface/LR-: J26.7, J27.13, J27.14, J28.7
/Interface/MAIN_POWER: J20.17, J21.17, J22.33, J22.34
/Interface/MODE_A: J20.5, J21.5, J22.9, J22.10, J29.4, J30.4
/Interface/MODE_B: J20.6, J21.6, J22.11, J22.12, J30.12, J31.4
/Interface/PASSENGER_HEATED_SEAT_STATUS: J23.4, J24.4, J32.2, J34.1
/Interface/PASSENGER_SEAT_TEMP_CONTROL: J24.12, J25.4, J32.12, J34.6
/Interface/PASSENGER_SUNLOAD: J18.14, J19.6, J32.13, J33.7
/Interface/REAR_DEFOG: J23.1, J24.1, J32.19, J33.10
/Interface/RECIRCULATION_A: J20.7, J21.7, J22.13, J22.14, J29.3, J30.3
/Interface/RECIRCULATION_B: J20.8, J21.8, J22.15, J22.16, J30.11, J31.3
/Interface/RF+: J26.11, J27.21, J27.22, J28.11
/Interface/RF-: J26.12, J27.23, J27.24, J28.12
/Interface/RIGHT_AIR_TEMP_CONTROL_A: J20.3, J21.3, J22.5, J22.6, J29.2, J30.2
/Interface/RIGHT_AIR_TEMP_CONTROL_B: J20.4, J21.4, J22.7, J22.8, J30.10, J31.2
/Interface/RR+: J26.6, J27.11, J27.12, J28.6
/Interface/RR-: J26.5, J27.9, J27.10, J28.5
/Interface/SENSE1: J32.22, J34.11
/Interface/TRIGGER1: J32.20, J34.10
/Interface/UPPER_LEFT_AIR_TEMP: J18.16, J19.8, J32.17, J33.9
/Interface/UPPER_RIGHT_AIR_TEMP: J17.8, J18.8, J32.5, J33.3
/Interface/WHEEL_CONTROLS_SIGNAL: J20.12, J22.23, J35.7, J36.7
/Interface/WHEEL_CONTROLS_SUPPLY: J21.12, J22.24, J35.6, J36.6
GND: J17.1, J18.1, J18.9, J19.1, J20.18, J20.19, J20.20, J21.15, J21.18, J21.19, J21.20, J22.30, J22.35, J22.36, J22.37, J22.38, J22.39, J22.40, J26.17, J26.18, J26.19, J26.20, J27.33, J27.34, J27.35, J27.36, J27.37, J27.38, J27.39, J27.40, J28.17, J28.18, J28.19, J28.20, J29.5, J29.7, J30.5, J30.7, J32.7, J32.24, J32.25, J32.26, J32.33, J32.34, J32.35, J32.36, J32.37, J32.38, J32.39, J32.40, J33.4, J33.12, J33.13, J33.17, J33.18, J33.19, J33.20, J34.12, J34.13, J34.17, J34.18, J34.19, J34.20, J35.9, J35.10, J35.12, J36.9, J36.10, J36.12, J36.21, J36.22, J37.9, J37.10, J38.1, J39.1, J40.1, J41.1

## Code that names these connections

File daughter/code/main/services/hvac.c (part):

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#define AIN6	6
#define AIN7	7
#define AIN8	8
#define AIN9	9
#define AIN10	10
#define AIN11	11

#define ADC_CHANNELS 12                  /*!< Data buffer length of test buffer */

#define INSIDE_AIR_TEMP										AIN0
#define AMBIENT_AIR_TEMP  		 						AIN1
#define UPPER_RIGHT_AIR_TEMP   						AIN2
#define UPPER_LEFT_AIR_TEMP   						AIN3
#define LOWER_RIGHT_AIR_TEMP   						AIN4
#define LOWER_LEFT_AIR_TEMP   						AIN5
#define AMBIENT_LIGHT				   						AIN6
#define DRIVER_SUNLOAD				  					AIN7
#define PASSENGER_SUNLOAD									AIN8

#define LEFT_AIR_TEMP_CONTROL_A						A0
#define LEFT_AIR_TEMP_CONTROL_B						A1
#define RIGHT_AIR_TEMP_CONTROL_A					A2
#define RIGHT_AIR_TEMP_CONTROL_B					A3
#define MODE_A														A4
#define MODE_B														A5
#define RECIRCULATION_A										A6
#define RECIRCULATION_B										A7

#define DRIVER_SEAT_TEMP_CONTROL					B0
#define PASSENGER_SEAT_TEMP_CONTROL				B1
#define INSIDE_AIR_TEMP_BLOWER						B2
#define BLOWER_MOTOR											B3
#define REAR_DEFOG												B4
#define DRIVER_HEATED_SEAT_STATUS					B6
#define PASSENGER_HEATED_SEAT_STATUS			B7

#define ACTUATOR_PULSE_WIDTH							100
#define ACTUATOR_PULSE_WIDTH							200
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	char type[100];
	cJSON * payload = NULL;

	mcp23x17_set_mode(&mcp_dev, DRIVER_HEATED_SEAT_STATUS, MCP23X17_GPIO_INPUT);
	mcp23x17_set_mode(&mcp_dev, PASSENGER_HEATED_SEAT_STATUS, MCP23X17_GPIO_INPUT);

	set_mode("init");

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
void actuator_init()
{
    actuators[LEFT_AIR].pinA = LEFT_AIR_TEMP_CONTROL_A;
		actuators[LEFT_AIR].pinB = LEFT_AIR_TEMP_CONTROL_B;
    actuators[LEFT_AIR].currentPosition = 45;
    actuators[LEFT_AIR].targetPosition = 0;
		actuators[LEFT_AIR].duration = 1;
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		actuators[LEFT_AIR].isSpinning = false;
		strcpy(actuators[LEFT_AIR].id, "LEFT_AIR");

	  actuators[RIGHT_AIR].pinA = RIGHT_AIR_TEMP_CONTROL_A;
		actuators[RIGHT_AIR].pinB = RIGHT_AIR_TEMP_CONTROL_B;
	  actuators[RIGHT_AIR].currentPosition = 45;
    actuators[RIGHT_AIR].targetPosition = 0;
		actuators[RIGHT_AIR].duration = 1;
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		actuators[RIGHT_AIR].isSpinning = false;
		strcpy(actuators[RIGHT_AIR].id, "RIGHT_AIR");

		actuators[MODE].pinA = MODE_A;
		actuators[MODE].pinB = MODE_B;
	  actuators[MODE].currentPosition = 350;
    actuators[MODE].targetPosition = 0;
		actuators[MODE].duration = 1;
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		actuators[MODE].isSpinning = false;
		strcpy(actuators[MODE].id, "MODE");

		actuators[RECIRCULATION].pinA = RECIRCULATION_A;
		actuators[RECIRCULATION].pinB = RECIRCULATION_B;
	  actuators[RECIRCULATION].currentPosition = 0;
    actuators[RECIRCULATION].targetPosition = 0;
		actuators[RECIRCULATION].duration = 1;
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	timer_main();
	actuator_init();

  mcp23x17_set_mode(&mcp_dev, DRIVER_HEATED_SEAT_STATUS, MCP23X17_GPIO_INPUT);
  mcp23x17_set_mode(&mcp_dev, PASSENGER_HEATED_SEAT_STATUS, MCP23X17_GPIO_INPUT);

  mcp23x17_set_mode(&mcp_dev, LEFT_AIR_TEMP_CONTROL_A, MCP23X17_GPIO_OUTPUT);
	mcp23x17_set_mode(&mcp_dev, LEFT_AIR_TEMP_CONTROL_B, MCP23X17_GPIO_OUTPUT);
	mcp23x17_set_mode(&mcp_dev, RIGHT_AIR_TEMP_CONTROL_A, MCP23X17_GPIO_OUTPUT);
	mcp23x17_set_mode(&mcp_dev, RIGHT_AIR_TEMP_CONTROL_B, MCP23X17_GPIO_OUTPUT);
	mcp23x17_set_mode(&mcp_dev, MODE_A, MCP23X17_GPIO_OUTPUT);
	mcp23x17_set_mode(&mcp_dev, MODE_B, MCP23X17_GPIO_OUTPUT);
	mcp23x17_set_mode(&mcp_dev, RECIRCULATION_A, MCP23X17_GPIO_OUTPUT);
	mcp23x17_set_mode(&mcp_dev, RECIRCULATION_B, MCP23X17_GPIO_OUTPUT);
	mcp23x17_set_mode(&mcp_dev, DRIVER_SEAT_TEMP_CONTROL, MCP23X17_GPIO_OUTPUT);
	mcp23x17_set_mode(&mcp_dev, PASSENGER_SEAT_TEMP_CONTROL, MCP23X17_GPIO_OUTPUT);
	mcp23x17_set_mode(&mcp_dev, INSIDE_AIR_TEMP_BLOWER, MCP23X17_GPIO_OUTPUT);
	mcp23x17_set_mode(&mcp_dev, REAR_DEFOG, MCP23X17_GPIO_OUTPUT);
	mcp23x17_set_mode(&mcp_dev, BLOWER_MOTOR, MCP23X17_GPIO_OUTPUT);

  mcp23x17_set_interrupt(&mcp_dev, DRIVER_HEATED_SEAT_STATUS, MCP23X17_INT_ANY_EDGE);
  mcp23x17_set_interrupt(&mcp_dev, PASSENGER_HEATED_SEAT_STATUS, MCP23X17_INT_ANY_EDGE);
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
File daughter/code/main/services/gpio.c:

#include <stdio.h>
#include <string.h>
#include <stdlib.h>
#include "freertos/FreeRTOS.h"
#include "freertos/task.h"
#include "freertos/queue.h"
#include "driver/gpio.h"
#include "driver/gpio.h"
#include <string.h>

#define IGNITION_WIRE_IO CONFIG_IGNITION_WIRE_IO
#define MAIN_POWER_IO CONFIG_MAIN_POWER_IO
#define DISPLAY_POWER_IO CONFIG_DISPLAY_POWER_IO
#define AUDIO_STBY_IO CONFIG_AUDIO_STBY_IO
#define AUDIO_MUTE_IO CONFIG_AUDIO_MUTE_IO
#define J1850_INPUT_PIN CONFIG_J1850_INPUT_PIN
#define J1850_OUTPUT_PIN CONFIG_J1850_OUTPUT_PIN
#define J1850_DEBUG_PIN 14
#define EXT_AMP_IO 27

#define INTA_GPIO 25
#define INTB_GPIO 26

#define GPIO_OUTPUT_PIN_SEL  ((1ULL<<J1850_DEBUG_PIN) | (1ULL<<J1850_OUTPUT_PIN) | (1ULL<<MAIN_POWER_IO) | (1ULL<<EXT_AMP_IO) | (1ULL<<DISPLAY_POWER_IO) | (1ULL<<AUDIO_STBY_IO) | (1ULL<<AUDIO_MUTE_IO))
#define GPIO_INPUT_PIN_SEL  ((1ULL<<IGNITION_WIRE_IO) | (1ULL<<J1850_INPUT_PIN) | (1ULL<<INTA_GPIO) | (1ULL<<INTA_GPIO))
#define ESP_INTR_FLAG_DEFAULT 0

#define SDA_GPIO 21
#define SCL_GPIO 22


// static void IRAM_ATTR intr_handler(void *arg)
// {
//     printf("Interrupt!\n");
// }

void gpio_main(void)
{
    gpio_config_t io_conf;
    io_conf.intr_type = GPIO_INTR_DISABLE;
    io_conf.mode = GPIO_MODE_OUTPUT;
    io_conf.pin_bit_mask = GPIO_OUTPUT_PIN_SEL;
    io_conf.pull_down_en = 0;
    io_conf.pull_up_en = 0;
    gpio_config(&io_conf);

    io_conf.intr_type = GPIO_INTR_ANYEDGE;
    io_conf.pin_bit_mask = GPIO_INPUT_PIN_SEL;
    io_conf.mode = GPIO_MODE_INPUT;
    io_conf.pull_up_en = 0;
    gpio_config(&io_conf);

    gpio_install_isr_service(ESP_INTR_FLAG_DEFAULT);
}

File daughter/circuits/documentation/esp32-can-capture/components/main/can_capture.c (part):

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
// GPIO assignments
#define GPIO_STATUS_LED               (GPIO_NUM_2)
#define GPIO_CAN_RX                   (GPIO_NUM_4)
// #define GPIO_CAN_TX                   (GPIO_NUM_???)
#define GPIO_MAINBOARD_SOFT_POWER     (GPIO_NUM_5)
#define GPIO_DISPLAY_POWER            (GPIO_NUM_15)
#define GPIO_AUDIO_AMP_POWER          (GPIO_NUM_16)
#define GPIO_MAINBOARD_POWER          (GPIO_NUM_18)

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void initialize_gpio() {
  gpio_set_direction(GPIO_STATUS_LED, GPIO_MODE_OUTPUT);
  gpio_set_direction(GPIO_MAINBOARD_SOFT_POWER, GPIO_MODE_OUTPUT);
  gpio_set_direction(GPIO_DISPLAY_POWER, GPIO_MODE_OUTPUT);
  gpio_set_direction(GPIO_AUDIO_AMP_POWER, GPIO_MODE_OUTPUT);
  gpio_set_direction(GPIO_MAINBOARD_POWER, GPIO_MODE_OUTPUT);
}
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apply power to peripherals
***/
void apply_dash_power() {
  gpio_set_level(GPIO_DISPLAY_POWER, 0); //display power
  gpio_set_level(GPIO_AUDIO_AMP_POWER, 0); //audio amp power
  gpio_set_level(GPIO_MAINBOARD_POWER, 0); //mainboard power
  gpio_set_level(GPIO_MAINBOARD_SOFT_POWER, 0); //mainboard softpower
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
  // configure CAN receiver
  CAN_cfg.rx_queue = xQueueCreate(10, sizeof(CAN_frame_t));
  CAN_cfg.rx_pin_id = GPIO_CAN_RX;
  CAN_cfg.speed = 50;

  //start CAN module
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
      if (NewIgnitionState != IgnitionUnknown) {
        if (NewIgnitionState != IgnitionState) {
          ESP_LOGI("canbus", "ignition state change from %s to %s", get_ignition_state_label(IgnitionState), get_ignition_state_label(NewIgnitionState));
          if (NewIgnitionState == IgnitionRun) {
						dash_wait_flag = true;
	  			}
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          IgnitionState = NewIgnitionState;
          
        } else {
          //ESP_LOGI("canbus", "repeat ignition state %s", get_ignition_state_label(IgnitionState));
        }
      }

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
